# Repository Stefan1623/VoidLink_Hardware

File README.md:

# Voidlink_Hardware

VoidLink feautures a 4-layer PCB that integrates the RP2350 MCU with the SX1262 transceiver. It also contains custom power circuitry that uses USB or battery power with battery charging and under voltage protection.

Version Notes:

    V1 only integrates the MCU and must interface with an external transceiver through the provided pinout.

    V2 fully integrates both the MCU and the transceiver.

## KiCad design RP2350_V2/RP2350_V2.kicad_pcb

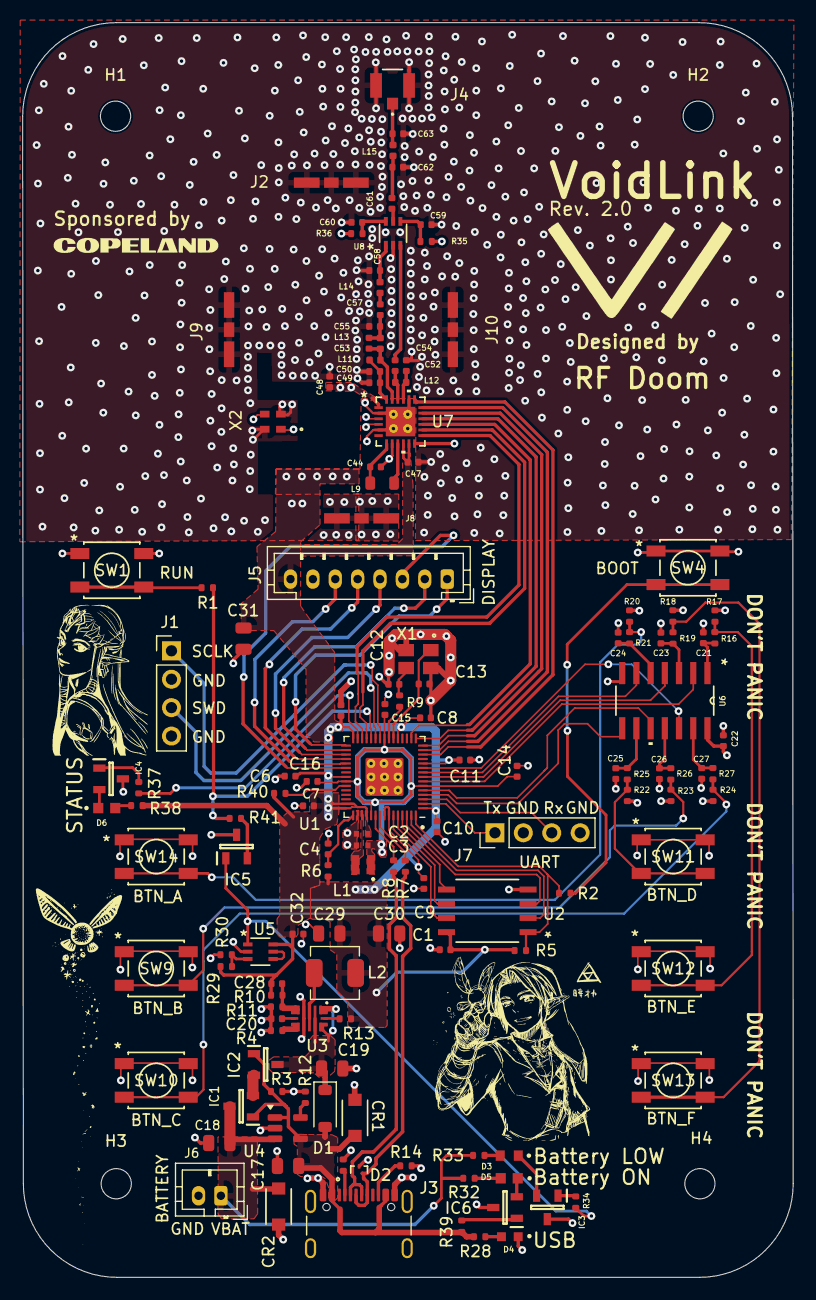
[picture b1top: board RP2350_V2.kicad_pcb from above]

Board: 4 copper layers, 68.9 x 112.1 mm, 142 parts (0 on the bottom side), 102 nets.

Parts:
C1, C5, C6, C7, C8, C9, C10, C11, C14, C16, C47: 100n; C_0402_1005Metric
C2, C3: 4.7u; C_0402_1005Metric_small_pads
C4, C15: 4.7u; C_0402_1005Metric
C12, C13: 15p; C_0402_1005Metric
C17, C18: 4.7u; C_0805_2012Metric
C19, C30, C31: 22u; C_0805_2012Metric
C20: 4.7n; C_0402_1005Metric
C21, C22, C23, C24, C25, C26, C27, C32: 0.1u; C_0402_1005Metric
C28: 10p; C_0402_1005Metric
C29: 10u; C_0805_2012Metric
C44: 470n; C_0402_1005Metric
C48: 1u; C_0402_1005Metric
C49: 47n; C_0402_1005Metric
C50: 47p; C_0402_1005Metric
C52, C58: 1.8p; C_0402_1005Metric
C53: 3p; C_0402_1005Metric
C54: 2.4p; C_0402_1005Metric
C55: 5.6p; C_0402_1005Metric
C57, C61: 39p; C_0402_1005Metric
C59, C60: 1n; C_0402_1005Metric
C62, C63: 3.3p; C_0402_1005Metric
CR1, CR2: SMF12CA; SMFSeries_SOD-123F
D1: MBR0520LT; D_SOD-123
D2: ESD7L5.0DT5G; SOT-723_0P85X1P25_ONS-L
D3: LTW-C193DS5-ND; LEDC1608X35N_red
D4: LTST-C190TBKT; LEDM1608X80_blue
D5: LTST-C193TGKT-5A; LEDC1608X55N_orange
D6: LTST-C191KFKT; LEDC1608X55N_orange
H1, H2, H3, H4: MountingHole; MountingHole_2.7mm_M2.5
IC1, IC2, IC3, IC4, IC5, IC6: DMP1045U-7; SOT96P240X110-3N
J1, J7: Conn_01x04_Pin; PinHeader_1x04_P2.54mm_Vertical
J2, J8, J9, J10: S0991-46R; HARWIN_S0991-46R
J3: USB_C_Receptacle_USB2.0_16P; USB_C_Receptacle_GCT_USB4105-xx-A_16P_TopMnt_Horizontal
J4: IPEX1; MHF I_RECE_IPX
J5: Conn_01x08_Socket; JST_PH_B8B-PH-K_1x08_P2.00mm_Vertical
J6: Conn_01x02_Pin; JST_PH_B2B-PH-K_1x02_P2.00mm_Vertical
L1: 3.3u; AOTA-B201610S3R3-101-T
L2: 560n; L_Changjiang_FXL0420
L9: 15u; L_0805_2012Metric
L11: 47n; L_0402_1005Metric
L12: 15n; L_0402_1005Metric
L13: 2.5n; L_0402_1005Metric
L14: 4.7n; L_0402_1005Metric
L15: 9.1n; L_0402_1005Metric
R1, R2, R9, R40, R41: 1k; R_0402_1005Metric
R3, R13, R34, R37, R39: 100k; R_0402_1005Metric
R4: 8.06k; R_0402_1005Metric
R5, R12, R16, R17, R18, R19, R20, R21, R22, R23, R24, R25, R26, R27: 10k; R_0402_1005Metric
R6: 33; R_0402_1005Metric
R7, R8: 27; R_0402_1005Metric
R10: 88.7k; R_0402_1005Metric
R11: 19.6k; R_0402_1005Metric
R14, R15: 5.1k; R_0402_1005Metric
R28: 110; R_0402_1005Metric
R29: 1.5Meg; R_0402_1005Metric
R30: 1Meg; R_0402_1005Metric
R32: 91; R_0402_1005Metric
R33: 20; R_0402_1005Metric
R35, R36: 100; R_0402_1005Metric
R38: 51; R_0402_1005Metric
SW1, SW4, SW9, SW10, SW11, SW12, SW13, SW14: PTS 647 SN50 SMTR2 LFS
U1: RP2350_60QFN; RP2350-QFN-60-1EP_7x7_P0.4mm_EP3.4x3.4mm_ThermalVias_NEW
U2: W25Q128JVS; SOIC_128JVSIQ_WIN
U3: TPS62811QWRWYRQ1; RWY0009A
U4: MCP73812T-420I-OT; SOT-23-5
U5: TLV3012AIDCKR; DCK6
U6: 74HC14; SN74HC14DR_D14
U7: SX1262_QFN24_4X4_SEM
U8: PE4259_RF_SW
X1: ABM8-272-T3; ABM8-272-T3_ABR
X2: NX2016SA-32M-EXS00A-CS06465; NX2016SA_NDK

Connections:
+1V1: C3.1, C14.1, C15.1, C16.1, L1.1, U1.6 (DVDD), U1.23 (DVDD), U1.39 (DVDD), U1.50 (VREG_FB)
+3V3: C1.1, C2.1, C5.1, C6.1, C7.1, C8.1, C9.1, C10.1, C11.1, C22.2, C28.1, C29.1, C30.1, C31.1, C32.1, C47.2, C48.2, J5.8, L2.2, R5.1, R6.1, R10.1, R13.1, R17.1, R18.1, R20.1, R22.1, R23.1, R24.1, R29.1, R36.2, R38.1, R40.2, U1.1 (IOVDD), U1.11 (IOVDD), U1.20 (IOVDD), U1.30 (IOVDD), U1.38 (IOVDD), U1.44 (ADC_AVDD), U1.45 (IOVDD), U1.49 (VREG_VIN), U1.53 (USB_OTP_VDD), U1.54 (QSPI_IOVDD), U2.8 (VCC), U5.6 (V+), U6.14 (VCC), U7.1 (VDD_IN), U7.10 (VBAT), U7.11 (VBAT_IO)
/BTN_BACK: U1.7 (GPIO4), U6.2
/BTN_MACRO_A: U1.4 (GPIO2), U6.8
/BTN_MACRO_B: U1.5 (GPIO3), U6.10
/BTN_MACRO_C: U1.10 (GPIO7), U6.12
/BTN_NEXT: U1.9 (GPIO6), U6.6
/BTN_OK: U1.8 (GPIO5), U6.4
/COMP_FSET: R4.1, U3.7 (COMP_FSET)
/Converter_In: C19.1, D1.1 (K), IC2.3 (D), U3.1 (MODE_SYNC), U3.2 (VIN), U3.8 (EN)
/Converter_Out: L2.1, U3.3 (SW)
/DISPLAY_BUSY: J5.1, U1.31 (GPIO19)
/DISPLAY_DC: J5.3, U1.36 (GPIO24)
/DISPLAY_RESET: J5.2, U1.32 (GPIO20)
/FB: C28.2, R10.2, R11.1, U3.5 (FB)
/PG: R13.2, U3.9 (PG)
/QSPI_SCLK: U1.56 (QSPI_SCLK), U2.6 (CLK)
/QSPI_SD0: U1.57 (QSPI_SD0), U2.5 (DI(IO0))
/QSPI_SD1: U1.59 (QSPI_SD1), U2.2 (DO(IO1))
/QSPI_SD2: U1.58 (QSPI_SD2), U2.3 (IO2)
/QSPI_SD3: U1.55 (QSPI_SD3), U2.7 (IO3)
/QSPI_SS: R2.2, R5.2, U1.60 (QSPI_SS), U2.1 (~CS)
/RUN: R1.2, R41.2, U1.26 (RUN)
/RUN_IN: R1.1, SW1.3, SW1.4
/SPI1_CLK: J5.5, U1.34 (GPIO22)
/SPI1_CS: J5.4, U1.33 (GPIO21)
/SPI1_TX: J5.6, U1.35 (GPIO23)
/STATUS_LED: R37.1, U1.29 (GPIO18)
/SWCLK: J1.1, U1.24 (SWCLK)
/SWD: J1.3, U1.25 (SWD)
/SX1262/DIO2: R35.2, U7.12 (DIO2)
/SX1262/VR_PA: C49.2, C50.2, L11.2, U7.24 (VR_PA)
/SX1262/XTA: U7.3 (XTA), X2.3
/SX1262/XTB: U7.4 (XTB), X2.1
/UART_Rx_DEBUG: J7.3, U1.3 (GPIO1)
/UART_Tx_DEBUG: J7.1, U1.2 (GPIO0)
/USB_CC1: J3.A5 (CC1), R15.1
/USB_CC2: J3.B5 (CC2), R14.1
/USB_D+: D2.2 (K), J3.A6 (D+), J3.B6 (D+), R7.1
/USB_D-: D2.1 (K), J3.A7 (D-), J3.B7 (D-), R8.1
/UVLO_RST: IC5.1 (G), R34.1, U5.1 (OUT)
/VBAT: C18.1, CR2.1, IC1.3 (D), J6.1, R32.1, R33.1, U4.3 (V_{BAT})
/VREG_AVDD: C4.1, R6.2, U1.46 (VREG_AVDD)
/VREG_LX: L1.2, U1.48 (VREG_LX)
/XIN: C13.1, U1.21 (XIN), X1.1
/XOUT: R9.2, U1.22 (XOUT)
/~USB_BOOT: R2.1, SW4.3, SW4.4
CS/NSS: U1.13 (GPIO9), U7.19 (NSS)
DIO1: U1.28 (GPIO17), U7.13 (DIO1)
GND: C1.2, C2.2, C3.2, C4.2, C5.2, C6.2, C7.2, C8.2, C9.2, C10.2, C11.2, C12.1, C13.2, C14.2, C15.2, C16.2, C17.2, C18.2, C19.2, C20.2, C21.2, C22.1, C23.2, C24.2, C25.2, C26.2, C27.2, C29.2, C30.2, C31.2, C32.2, C44.1, C47.1, C48.1, C49.1, C50.1, C52.1, C55.1, C58.1, C59.2, C60.2, C62.1, C63.1, CR1.2, CR2.2, D2.3 (A), D4.C, IC3.3 (D), IC4.3 (D), IC5.3 (D), IC6.3 (D), J1.2, J1.4, J2.SH1 (SHIELD), J2.SH2 (SHIELD__1), J2.SH3 (SHIELD__2), J3.A1 (GND), J3.A12 (GND), J3.B1 (GND), J3.B12 (GND), J4.1, J4.2, J5.7, J6.2, J7.2, J7.4, J8.SH1 (SHIELD), J8.SH2 (SHIELD__1), J8.SH3 (SHIELD__2), J9.SH1 (SHIELD), J9.SH2 (SHIELD__1), J9.SH3 (SHIELD__2), J10.SH1 (SHIELD), J10.SH2 (SHIELD__1), J10.SH3 (SHIELD__2), R3.2, R4.2, R11.2, R12.2, R14.2, R15.2, R30.2, SW1.1, SW1.2, SW4.1, SW4.2, SW9.1, SW9.2, SW10.1, SW10.2, SW11.1, SW11.2, SW12.1, SW12.2, SW13.1, SW13.2, SW14.1, SW14.2, U1.47 (VREG_PGND), U1.61 (GND), U2.4 (GND), U3.4 (GND), U4.2 (V_{SS}), U5.2 (V-), U6.7 (GND), U7.2 (GND), U7.5 (GND), U7.8 (GND), U7.20 (GND), U7.25 (GND), U8.2 (GND), X1.2, X1.4, X2.2, X2.4
unnamed: C12.2, R9.1, X1.3
unnamed: C21.1, R16.2, U6.1
unnamed: C23.1, R19.2, U6.3
unnamed: C24.1, R21.2, U6.5
unnamed: C25.1, R25.2, U6.9
unnamed: C26.1, R26.2, U6.11
unnamed: C27.1, R27.2, U6.13
unnamed: C53.1, C55.2, C57.2, L13.2
unnamed: C57.1, L14.1
unnamed: C61.1, C62.2, L15.1
unnamed: C63.2, J4.3, L15.2
unnamed: D3.A, R33.2
unnamed: D4.A, R28.2
unnamed: D5.A, R32.2
unnamed: D6.A, R38.2
unnamed: IC1.2 (S), IC2.2 (S)
unnamed: IC3.1 (G), R34.2
unnamed: D3.C, IC3.2 (S)
unnamed: IC4.1 (G), R37.2
unnamed: D6.C, IC4.2 (S)
unnamed: IC5.2 (S), R41.1
unnamed: IC6.1 (G), R39.2
unnamed: D5.C, IC6.2 (S)
unnamed: R16.1, R17.2, SW12.3, SW12.4
unnamed: R18.2, R19.1, SW13.3, SW13.4
unnamed: R20.2, R21.1, SW14.3, SW14.4
unnamed: R22.2, R25.1, SW11.3, SW11.4
unnamed: R23.2, R26.1, SW9.3, SW9.4
unnamed: R24.2, R27.1, SW10.3, SW10.4
unnamed: R40.1, U1.40 (GPIO26_ADC0)
unnamed: R8.2, U1.51 (USB_DM)
unnamed: R7.2, U1.52 (USB_DP)
unnamed: C20.1, U3.6 (SS_TR)
unnamed: R12.1, U4.5 (PROG)
unnamed: R29.2, R30.1, U5.3 (IN+)
unnamed: U5.4 (IN-), U5.5 (REF)
unnamed: L9.2, U7.9 (DCC_SW)
unnamed: C54.2, L12.2, U7.22 (RFI_N)
unnamed: C52.2, L12.1, U7.21 (RFI_P)
unnamed: C53.2, L11.1, L13.1, U7.23 (RFO)
unnamed: C44.2, L9.1, U7.7 (VREG)
unnamed: C60.1, R36.1, U8.6 (*CTRL/VDD)
unnamed: C59.1, R35.1, U8.4 (CTRL)
unnamed: C58.2, L14.2, U8.1 (RF1)
unnamed: C54.1, U8.3 (RF2)
unnamed: C61.2, U8.5 (RFC)
SPI0_CLK: U1.14 (GPIO10), U7.18 (SCK)
SPI0_TX: U1.15 (GPIO11), U7.17 (MOSI)
SPIO_RX: U1.16 (GPIO12), U7.16 (MISO)
VBUS: C17.1, CR1.1, D1.2 (A), IC1.1 (G), IC2.1 (G), J3.A4 (VBUS), J3.A9 (VBUS), J3.B4 (VBUS), J3.B9 (VBUS), R3.1, R28.1, R39.1, U4.1 (CE), U4.4 (V_{DD})
uC_BUSY: U1.27 (GPIO16), U7.14 (BUSY)
uC_RESET: U1.17 (GPIO13), U7.15 (NRESET)

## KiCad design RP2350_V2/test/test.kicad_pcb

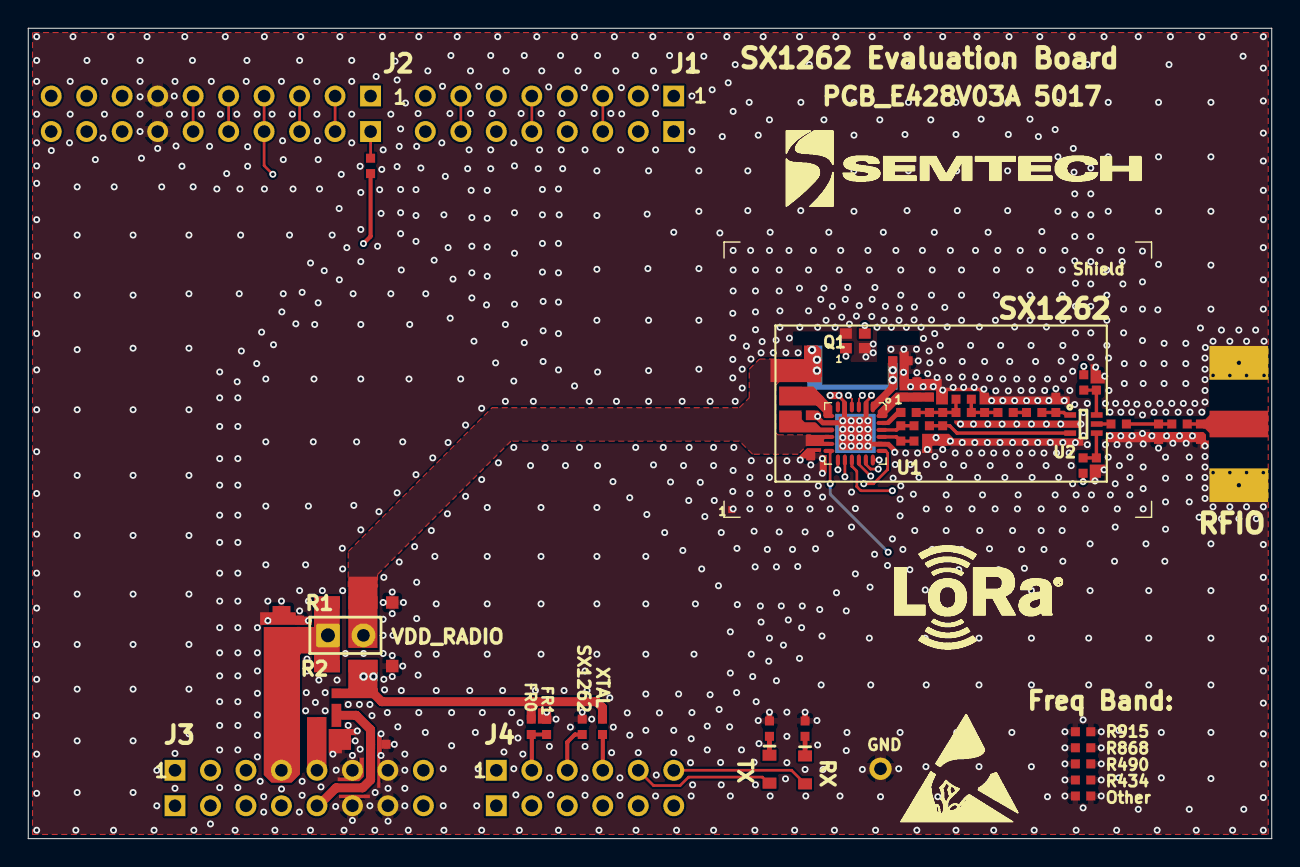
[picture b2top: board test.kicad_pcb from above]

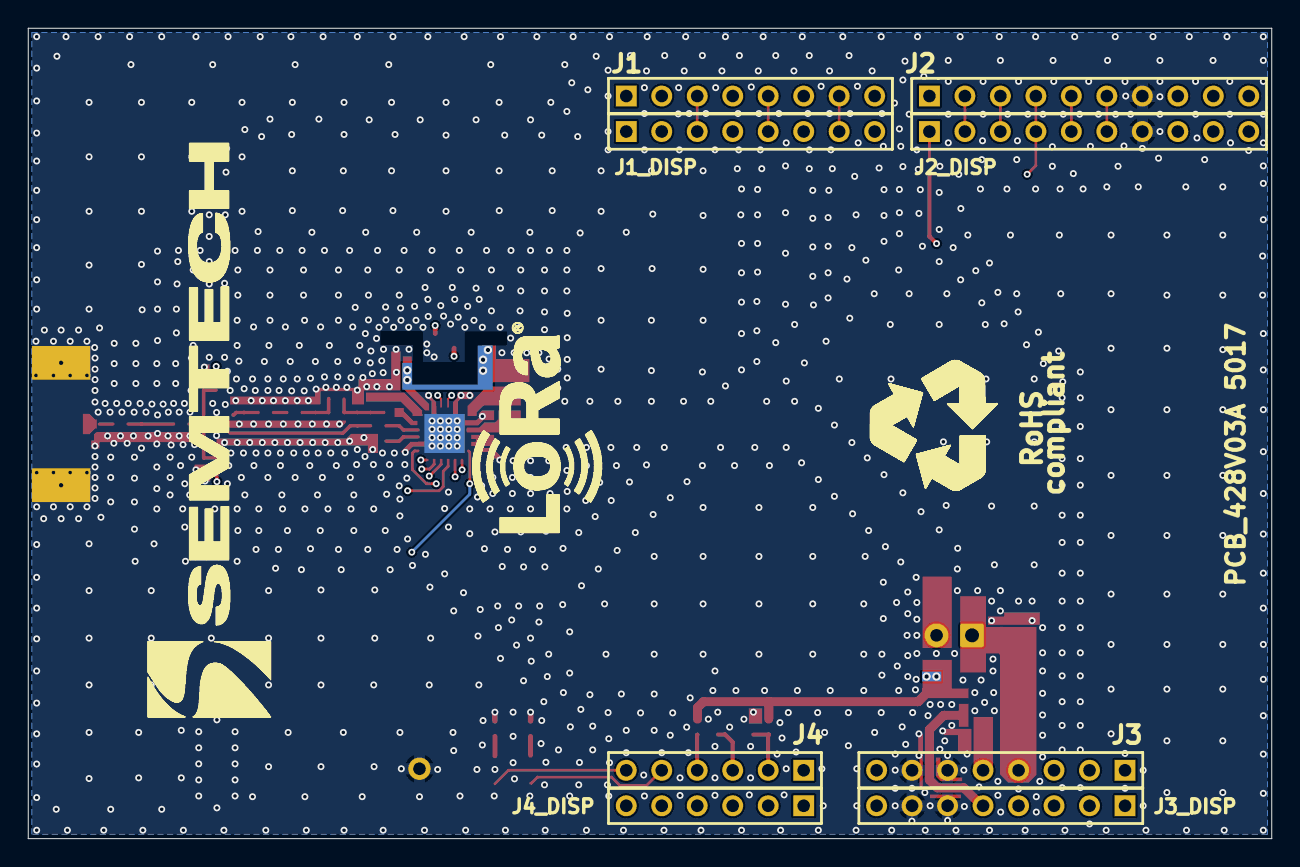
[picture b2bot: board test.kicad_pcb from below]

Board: 4 copper layers, 89.0 x 58.0 mm, 72 parts (11 on the bottom side), 47 nets.

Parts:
C1, C2, C3, C4, C5, C6, C7, C8, C9, C10, C11, C12, C13, C14, C15, C16, C17, C18, C23, C24: Cap; RLC_402_SMD
C20, C21: Cap; rlc_603_smd
C22, C26: Cap; rlc_805_smd
FR0, FR1: Resistor; RLC_402_SMD
GND: Test Pin; pin_0.9mm
J1, J1_DISP, J3, J3_DISP: Header 8; HDR1X8
J2, J2_DISP: Header 10; HDR1X10
J4, J4_DISP: Header 6; HDR1X6
L1, L2, L3, L4, L5, L6: Inductor; RLC_402_SMD
L7: Inductor; rlc_805_smd enlarged
Logo Bot: Logo symbol; logo_semtech_horiz_size4
Logo ESD: Logo symbol; Logo ESD
Logo Recycling1: Logo symbol; Logo Recycling1
Logo Semtech S: Logo symbol; logo_semtech_horiz_size3
Logo_LoRA1: Logo symbol; LOGO LORA SIZE4
Logo_LoRA2: Logo symbol; LOGO LORA SIZE3
Other: Resistor; RLC_402_SMD
Q1: Xtal; nd2016da
R1, R2: Resistor; rlc_603_smd
R3, R4, R11, R12, R13, R15, R16, R434, R868, R915: Resistor; RLC_402_SMD
R490: Resistor; rlc_402_smd
RFIO: SMA; SMA_end_launch_1.0mm_9.52mm
RX: LED; LGM676 LED
SX1262: Resistor; RLC_402_SMD
Shield: Logo symbol; BMIS-209-F - SHIELD - SOLDER_MASK
TX: LED; LGM676 LED
U1: SX1262; VQFN24_4X4MM
U2: PE4259 RF Switch; SC70-6
VDD_RADIO: Jumper; BRIDGE_254MM
XTAL: Resistor; rlc_402_smd

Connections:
ANT_SW: J2.1, R4.2
BUSY: J1.4, U1.14
DIO1: J1.6, U1.13
DIO2: R3.2, U1.12
DISP_RESET: J3.3, J3_DISP.3
F_CS: J1.7, J1_DISP.7
GND: C1.1, C2.1, C3.1, C5.1, C7.1, C9.1, C10.1, C12.1, C13.1, C14.2, C15.2, C16.1, C17.1, C18.1, C20.1, C21.1, C22.1, C23.1, C24.1, C26.1, FR1.1, GND.1, J2.7, J2_DISP.7, J3.6, J3.7, J3_DISP.6, J3_DISP.7, Other.1, Other.2, Q1.2, Q1.4, R15.1, R16.1, R434.1, R434.2, R490.1, R490.2, R868.1, R868.2, R915.1, R915.2, RFIO.2, SX1262.1, Shield.1, U1.2, U1.5, U1.8, U1.20, U1.25, U2.2
LED_RX: J4.6, RX.1
LED_TX: J4.5, TX.1
MISO: J2.5, J2_DISP.5, U1.16
MOSI: J2.4, J2_DISP.4, U1.17
NSS: J1.8, U1.19
NetC3_2: C3.2, C4.2, L1.1, L2.2, L3.1
NetC4_1: C4.1, C5.2, C6.2, L3.2
NetC6_1: C6.1, L4.1
NetC7_2: C7.2, L4.2, U2.1
NetC8_1: C8.1, C9.2, L5.1
NetC8_2: C8.2, U2.5
NetC10_2: C10.2, L5.2, RFIO.1
NetC11_1: C11.1, C13.2, U2.3
NetC11_2: C11.2, L6.2, U1.22
NetC12_2: C12.2, L6.1, U1.21
NetC14_1: C14.1, R4.1, U2.6
NetC15_1: C15.1, R3.1, U2.4
NetC17_2: C17.2, L7.1, U1.7
NetFR0_2: FR0.2, FR1.2, J4.2
NetJ4_3: J4.3, SX1262.2
NetL2_1: L2.1, U1.23
NetL7_2: L7.2, U1.9
NetR15_2: R15.2, TX.2
NetR16_2: R16.2, RX.2
OPT: J4.4, XTAL.2
SCK: J2.6, J2_DISP.6, U1.18
SD_CS: J2_DISP.1, R13.2
SX_NRESET: J4.1, U1.15
TFT_CS: J2.3, J2_DISP.3
TFT_D: J2.2, J2_DISP.2
T_CS: J1.5, J1_DISP.5
T_IRQ: J1.3, J1_DISP.3
VDD_3V3: C21.2, FR0.1, R2.1, R11.1, XTAL.1
VDD_MBED: C22.2, C23.2, J3.4, R1.2, R2.2, VDD_RADIO.1
VDD_RADIO: C16.2, C18.2, C20.2, R1.1, U1.1, U1.10, U1.11, VDD_RADIO.2
VDISPLAY: C24.2, J3_DISP.5, R11.2, R12.2, R13.1
VR_PA: C1.2, C2.2, L1.2, U1.24
VUSB: C26.2, J3.5, R12.1
XTA: Q1.3, U1.3
XTB: Q1.1, U1.4

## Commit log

2025-01-27 V1 init
2025-02-12 new power sch, rough lay floorplan
2025-02-15 First pass routing done! MCU pin updates. UVLO Reset resistor update
2025-02-16 Added LEDs, edege cuts, silkscreen logo
    next steps --> DRC
2025-02-16 DRC Clean (with waivers)
    Added manual vias to RP2350 GND pad.
    Silkscreen updates.
    Remaining DRCs seem waivable (TPS62811 footprint bug, USB C through holes, RP2350 footprint corners)
2025-02-19 sch updates, lay in progress
    updated TLV3012 package,
    changed cmos oscillator to xtal,
    updated LCSC component values for all non-generic components
2025-02-19 xtal lay done, JLC_DFM clean
2025-02-19 DONOT USE PREVIOUS VERSIONS! *Fixed TLV3012*, added TVS diodes
2025-02-20 Updated TVS diode to bi-directional version (SMF12CA)
2025-02-20 updated LED resistors, re-exported fabrication outputs
2025-02-21 caps added
2025-02-21 Rs added
2025-02-22 try again for BOM?
2025-02-26 updated manufacturing files, added orientation marker to TPS62811 in lay, no fiducial markers
    jlcpcb engineer asked me to confirm the orientation of the tps ic, i guess thats why we use pin 1 markers (flushed.png)
2025-02-27 MAJOR FIX - RP2350 unconnected 3V3, GND pins - previous versions will NOT work
    rip
2025-02-27 now rev1.1; improvements to 1v1 net, cleanup, local drc looks good
    lmnop
2025-03-04 initial transceier sch
2025-03-06 Rev 2.0 added. Ready to start transceiver layout.
2025-03-07 Transceiver components and schematic final?
2025-03-08 initial Transceiver layout
2025-03-10 progress :D
2025-03-10 VIASgit add --allgit add --all
2025-03-13 fix: remove lock file
2025-03-13 rev2 progress
2025-03-13 ggsdfsads
2025-03-14 optimizations
2025-03-16 Lots of Updatesgit add --allgit add --all
2025-03-16 optimizations, refinements
2025-03-16 added 3V3 input to ADC, fixed edge cut DRCs
2025-03-17 DFM progress
2025-03-17 vias smh my head
2025-03-17 final push?
2025-03-17 fix display pins on mcu
2025-03-18 dhfdbjfbd
2025-03-18 dfdjfjh pt2
2025-03-18 fixed RF impedance matched width, changed rf connector, etc.
    DRC+DFM clean with waivers. Pending final review for tapeout.
2025-03-18 update XTAL1 to X2, regen fab exports
2025-03-18 via refinement
2025-03-18 jhsdbdhjsvfdsm
2025-03-18 rev2.0 tapeout
2025-03-18 tapeout files included, updated D3, D5 LCSC values (change reflected in order)
